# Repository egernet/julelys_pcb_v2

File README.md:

# Julelys PCB v3

HAT (Hardware Attached on Top) til Orange Pi Zero 2 til styring af adresserbare SK6812 RGBW LED-strips.

## System Oversigt

```
Orange Pi Zero 2 ──► Julelys HAT ──► 8×55 SK6812 LED Matrix (440 LEDs)
        │                 │
        │ SPI @ 2.5 Mbps  │
        ▼                 ▼
  julelys_manager    ESP32-C3 (SPI slave)
                          │
                          ▼
                    74HC4051 MUX + Level Shifters
                          │
                          ▼
                    8x JST outputs
```

## Relaterede Repositories

| Repository | Beskrivelse |
|------------|-------------|
| [julelys_manager](https://github.com/egernet/julelys_manager) | Swift CLI + MCP server til LED-styring |
| [julelys_esp32](https://github.com/egernet/julelys_esp32/tree/feature/Hat) | ESP-IDF firmware (feature/Hat branch) |

## Features

- **ESP32-C3-WROOM-02** som SPI slave med RMT LED driver
- **8 LED-kanaler** via 74HC4051 multiplexer
- **Level shifting** (3.3V → 5V) via 74AHCT1G125
- **USB-C** til strøm og programmering (CP2102N)
- **Auto-reset** kredsløb til nem flashing
- **AI-styring** via Model Context Protocol (MCP)

## Nøglekomponenter

| Komponent | Funktion |
|-----------|----------|
| ESP32-C3-WROOM-02 | Hoved-MCU, SPI slave |
| CP2102N | USB-UART bridge |
| AMS1117-3.3 | 5V → 3.3V LDO |
| 74HC4051 | 8-kanal analog multiplexer |
| 74AHCT1G125 ×4 | Level shifters |

## Connectors

| Reference | Type | Funktion |
|-----------|------|----------|
| J1 | 2×13 Pin Socket | Orange Pi GPIO header |
| J4-J11 | JST B3B-XH-A ×8 | LED strip outputs |
| P1 | USB-C | Strøm + programmering |
| V_IN1, V_IN2 | Skrueterminal ×2 | Ekstern 5V (parallel, ~20A) |

## Strømkrav

- **LED strøm:** 8 strenge × 55 LEDs × 60mA = **26.4A max**
- Brug ekstern 5V PSU med tilstrækkelig kapacitet
- Ingen reverse polarity protection (fjernet pga. strømkrav)

## KiCad Filer

- `Julelys.kicad_pcb` - PCB layout
- `Julelys.kicad_sch` - Hovedskema
- `esp32.kicad_sch` - ESP32 subskema
- `power.kicad_sch` - Strømforsyning
- `untitled.kicad_sch` - USB-C og connectors

## Produktion

Produktionsfiler genereres til `production/`:
- Gerber filer (zipped)
- `bom.csv` - Stykliste
- `positions.csv` - Pick and place

## Licens

MIT

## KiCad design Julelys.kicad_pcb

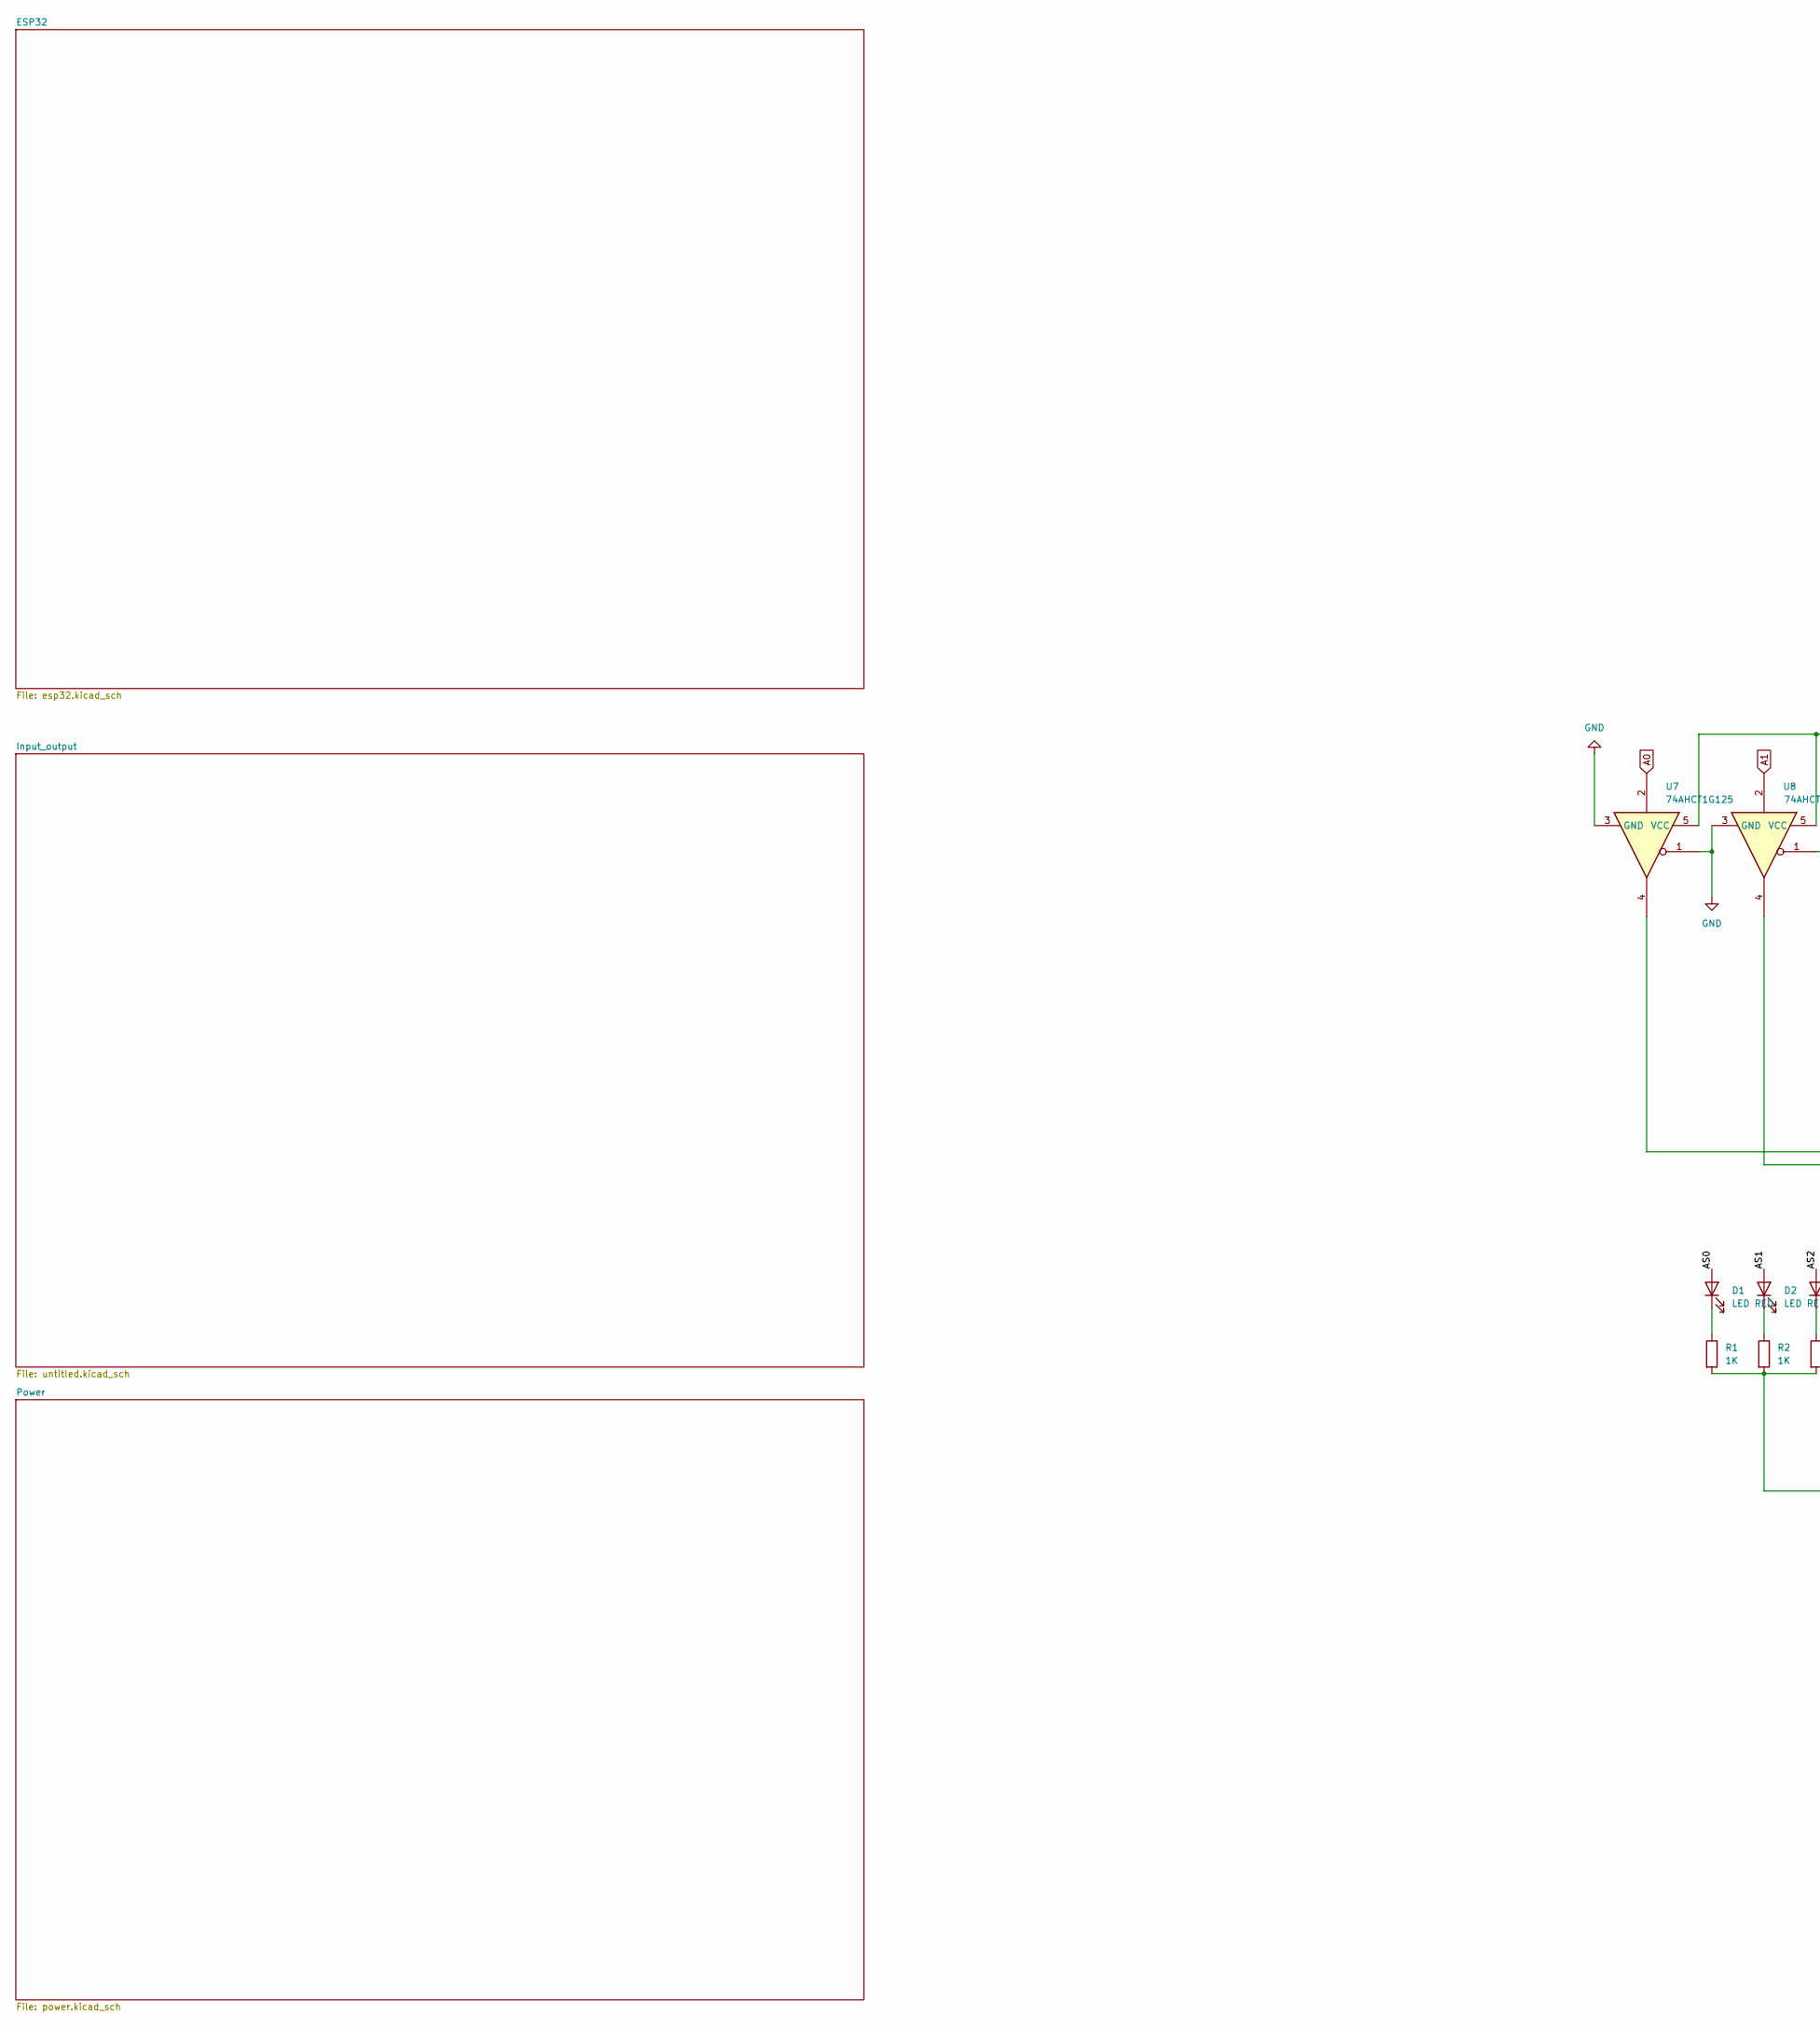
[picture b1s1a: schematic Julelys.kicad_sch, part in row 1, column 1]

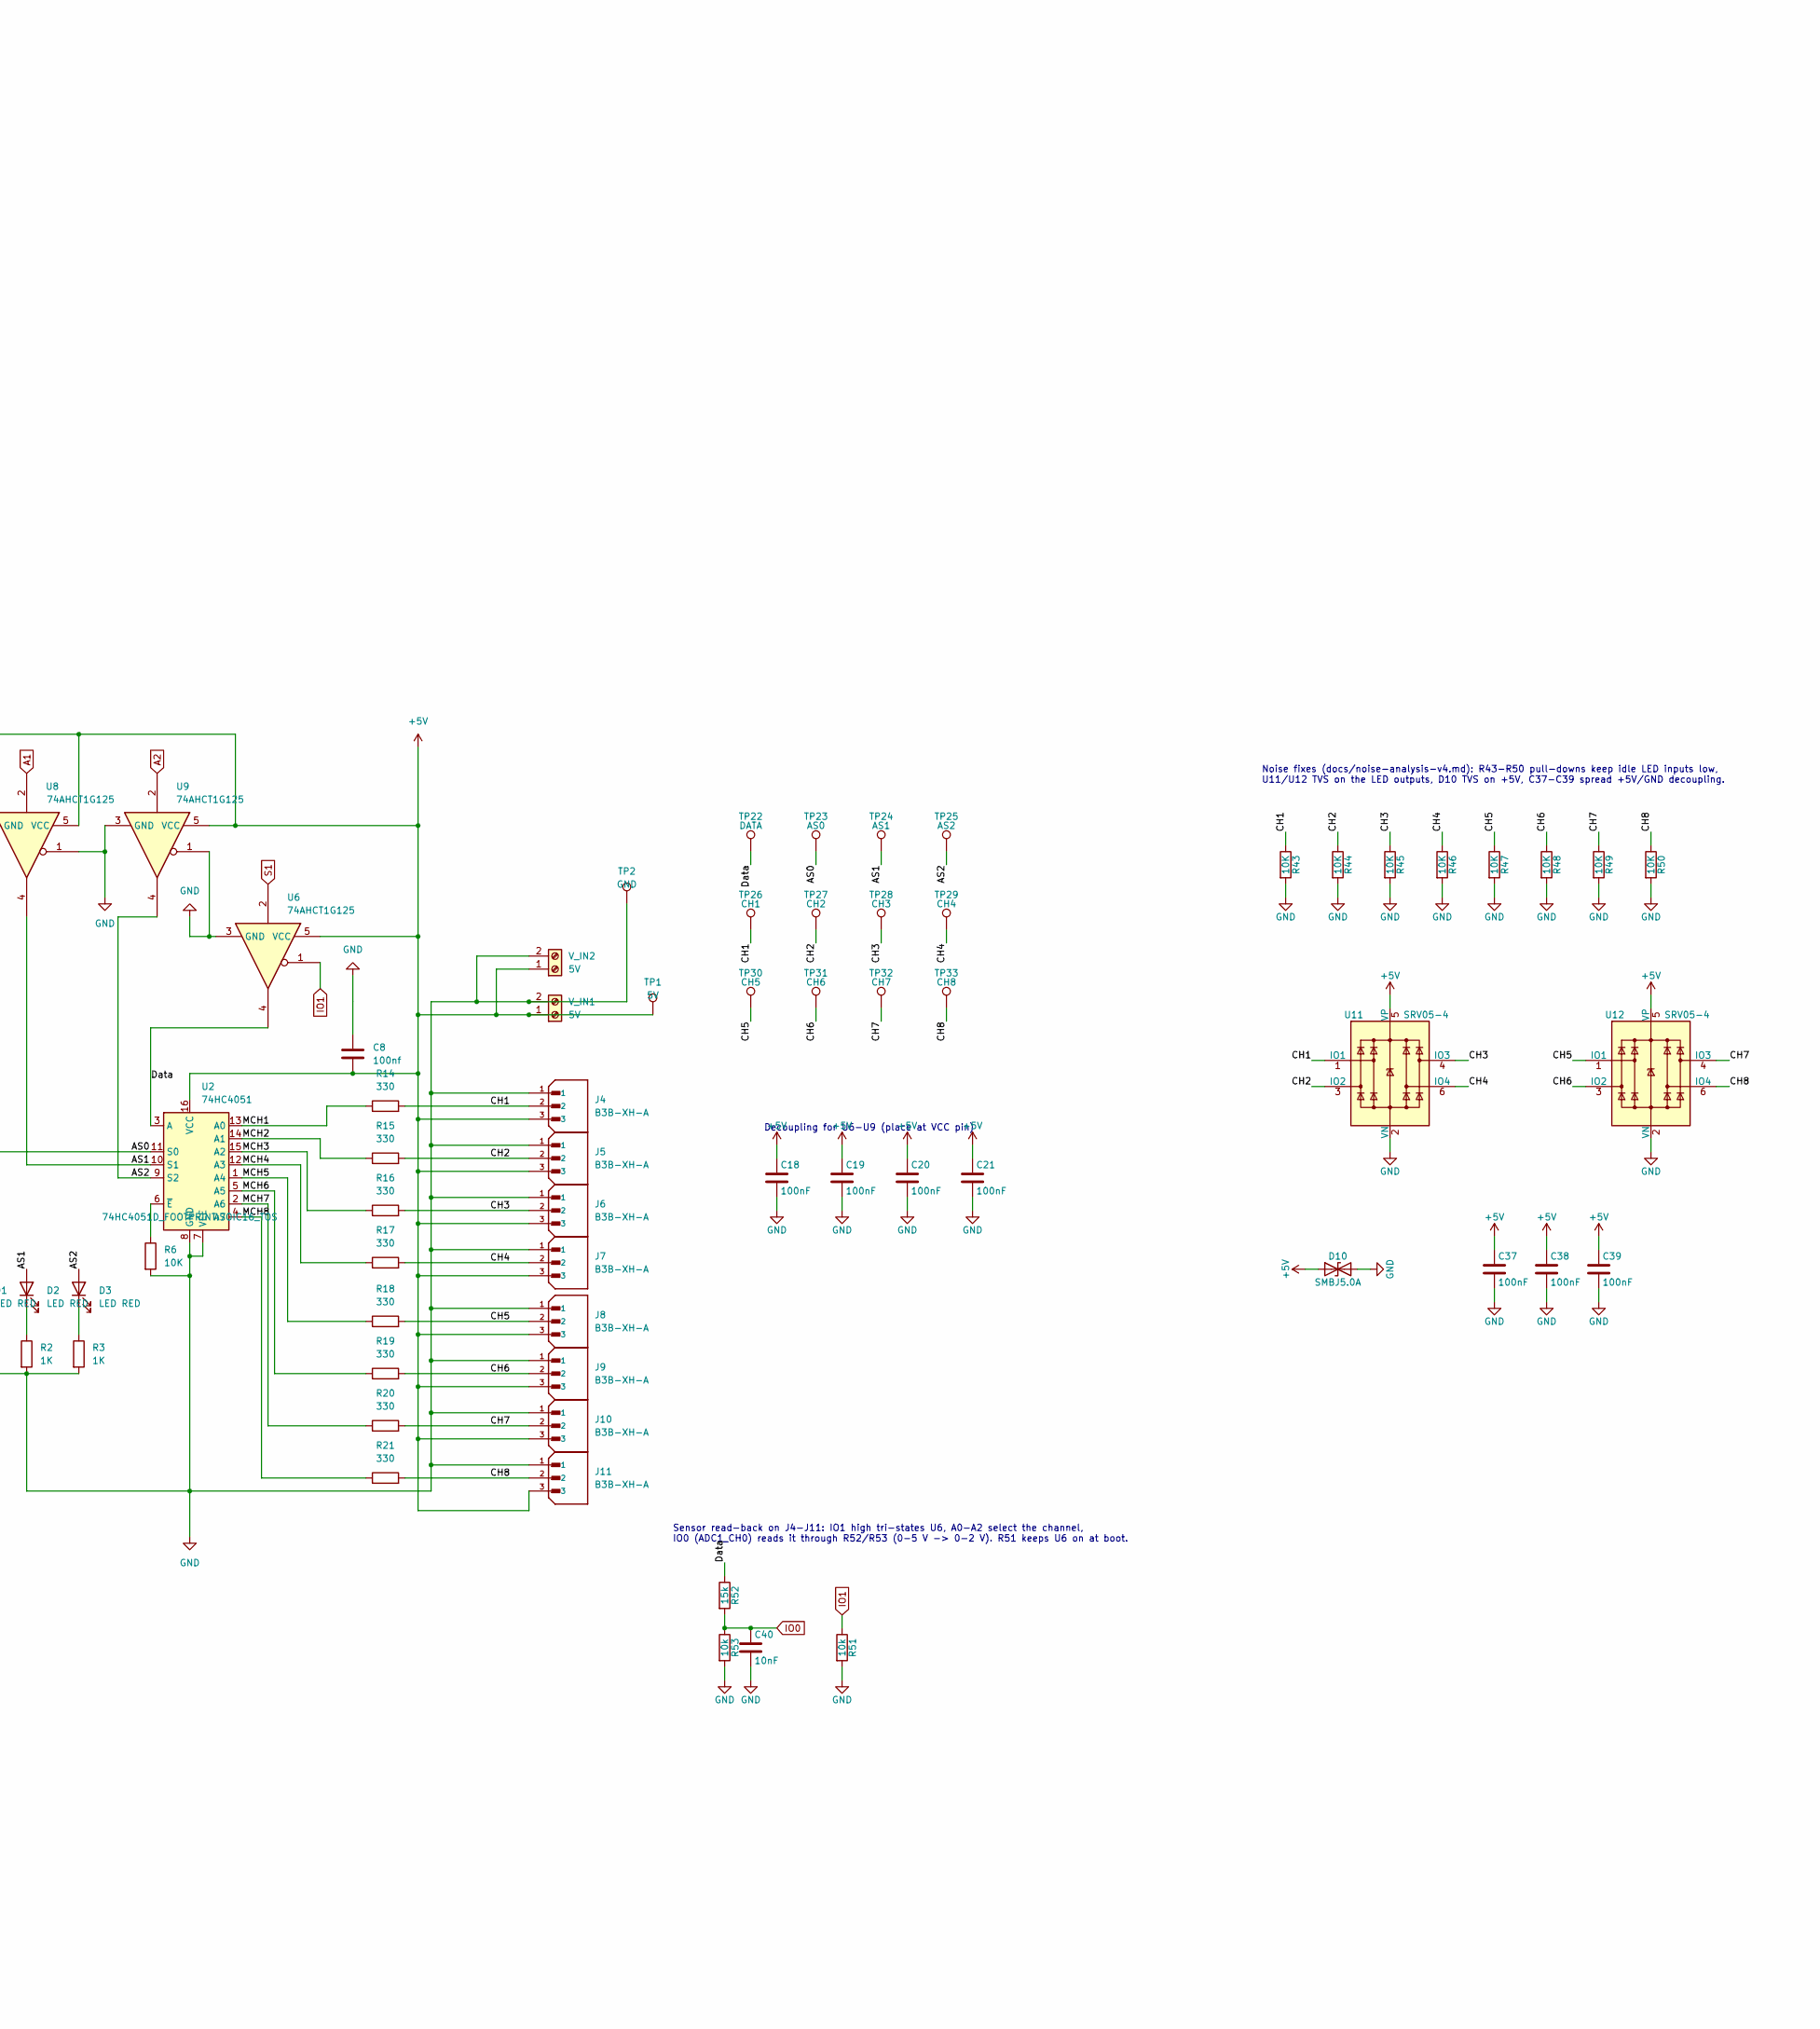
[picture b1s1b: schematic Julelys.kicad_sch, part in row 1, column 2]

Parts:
C8: 100nf; R_0603_1608Metric
C18, C19, C20, C21: 100nF; C_0603_1608Metric
C37, C38, C39: 100nF; C_0402_1005Metric
C40: 10nF; C_0402_1005Metric
D1, D2, D3: LED RED; LED_0805_2012Metric
D10: SMBJ5.0A; D_SMB
J4, J5, J6, J7, J8, J9, J10, J11: B3B-XH-A; JST_B3B-XH-A; PARTREV 7/4/21
R1, R2, R3: 1K; R_0603_1608Metric
R6: 10K; R_0603_1608Metric
R14, R15, R16, R17, R18, R19, R20, R21: 330; R_0603_1608Metric
R43, R44, R45, R46, R47, R48, R49, R50: 10K; R_0402_1005Metric
R51, R53: 10k; R_0402_1005Metric
R52: 15k; R_0402_1005Metric
TP1: 5V; TestPoint_Pad_1.0x1.0mm
TP2: GND; TestPoint_Pad_1.0x1.0mm
TP22: DATA; TestPoint_Pad_1.0x1.0mm
TP23: AS0; TestPoint_Pad_1.0x1.0mm
TP24: AS1; TestPoint_Pad_1.0x1.0mm
TP25: AS2; TestPoint_Pad_1.0x1.0mm
TP26: CH1; TestPoint_Pad_1.0x1.0mm
TP27: CH2; TestPoint_Pad_1.0x1.0mm
TP28: CH3; TestPoint_Pad_1.0x1.0mm
TP29: CH4; TestPoint_Pad_1.0x1.0mm
TP30: CH5; TestPoint_Pad_1.0x1.0mm
TP31: CH6; TestPoint_Pad_1.0x1.0mm
TP32: CH7; TestPoint_Pad_1.0x1.0mm
TP33: CH8; TestPoint_Pad_1.0x1.0mm
U2: 74HC4051; SOIC16_TOS
U6, U7, U8, U9: 74AHCT1G125; SOT-353_SC-70-5
U11, U12: SRV05-4; SOT-23-6
V_IN1, V_IN2: 5V; TerminalBlock_Altech_AK300-2_P5.00mm

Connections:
+5V: C8.2, C18.1, C19.1, C20.1, C21.1, C37.1, C38.1, C39.1, D10.1 (A1), J4.3, J5.3, J6.3, J7.3, J8.3, J9.3, J10.3, J11.3, TP1.1, U2.16 (VCC), U6.5 (VCC), U7.5 (VCC), U8.5 (VCC), U9.5 (VCC), U11.5 (VP), U12.5 (VP), V_IN1.1, V_IN2.1; also elsewhere on the board
/AS0: D1.2 (A), TP23.1, U2.11 (S0), U7.4
/AS1: D2.2 (A), TP24.1, U2.10 (S1), U8.4
/AS2: D3.2 (A), TP25.1, U2.9 (S2), U9.4
/CH1: J4.2, R14.2, R43.1, TP26.1, U11.1 (IO1)
/CH2: J5.2, R15.2, R44.1, TP27.1, U11.3 (IO2)
/CH3: J6.2, R16.2, R45.1, TP28.1, U11.4 (IO3)
/CH4: J7.2, R17.2, R46.1, TP29.1, U11.6 (IO4)
/CH5: J8.2, R18.2, R47.1, TP30.1, U12.1 (IO1)
/CH6: J9.2, R19.2, R48.1, TP31.1, U12.3 (IO2)
/CH7: J10.2, R20.2, R49.1, TP32.1, U12.4 (IO3)
/CH8: J11.2, R21.2, R50.1, TP33.1, U12.6 (IO4)
/Data: R52.1, TP22.1, U2.3 (A), U6.4
/MCH1: R14.1, U2.13 (A0)
/MCH2: R15.1, U2.14 (A1)
/MCH3: R16.1, U2.15 (A2)
/MCH4: R17.1, U2.12 (A3)
/MCH5: R18.1, U2.1 (A4)
/MCH6: R19.1, U2.5 (A5)
/MCH7: R20.1, U2.2 (A6)
/MCH8: R21.1, U2.4 (A7)
A0: U7.2; also elsewhere on the board
A1: U8.2; also elsewhere on the board
A2: U9.2; also elsewhere on the board
GND: C8.1, C18.2, C19.2, C20.2, C21.2, C37.2, C38.2, C39.2, C40.2, D10.2 (A2), J4.1, J5.1, J6.1, J7.1, J8.1, J9.1, J10.1, J11.1, R1.2, R2.2, R3.2, R6.2, R43.2, R44.2, R45.2, R46.2, R47.2, R48.2, R49.2, R50.2, R51.2, R53.2, TP2.1, U2.7 (VEE), U2.8 (GND), U6.3 (GND), U7.1, U7.3 (GND), U8.1, U8.3 (GND), U9.1, U9.3 (GND), U11.2 (VN), U12.2 (VN), V_IN1.2, V_IN2.2; also elsewhere on the board
IO0: C40.1, R52.2, R53.1; also elsewhere on the board
IO1: R51.1, U6.1; also elsewhere on the board
IO7: U6.2; also elsewhere on the board
unnamed: D1.1 (K), R1.1
unnamed: D2.1 (K), R2.1
unnamed: D3.1 (K), R3.1
unnamed: R6.1, U2.6 (~E)

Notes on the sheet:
Decoupling for U6-U9 (place at VCC pin)
Noise fixes (docs/noise-analysis-v4.md): R43-R50 pull-downs keep idle LED inputs low, U11/U12 TVS on the LED outputs, D10 TVS on +5V, C37-C39 spread +5V/GND decoupling.
Sensor read-back on J4-J11: IO1 high tri-states U6, A0-A2 select the channel, IO0 (ADC1_CH0) reads it through R52/R53 (0-5 V -> 0-2 V). R51 keeps U6 on at boot.

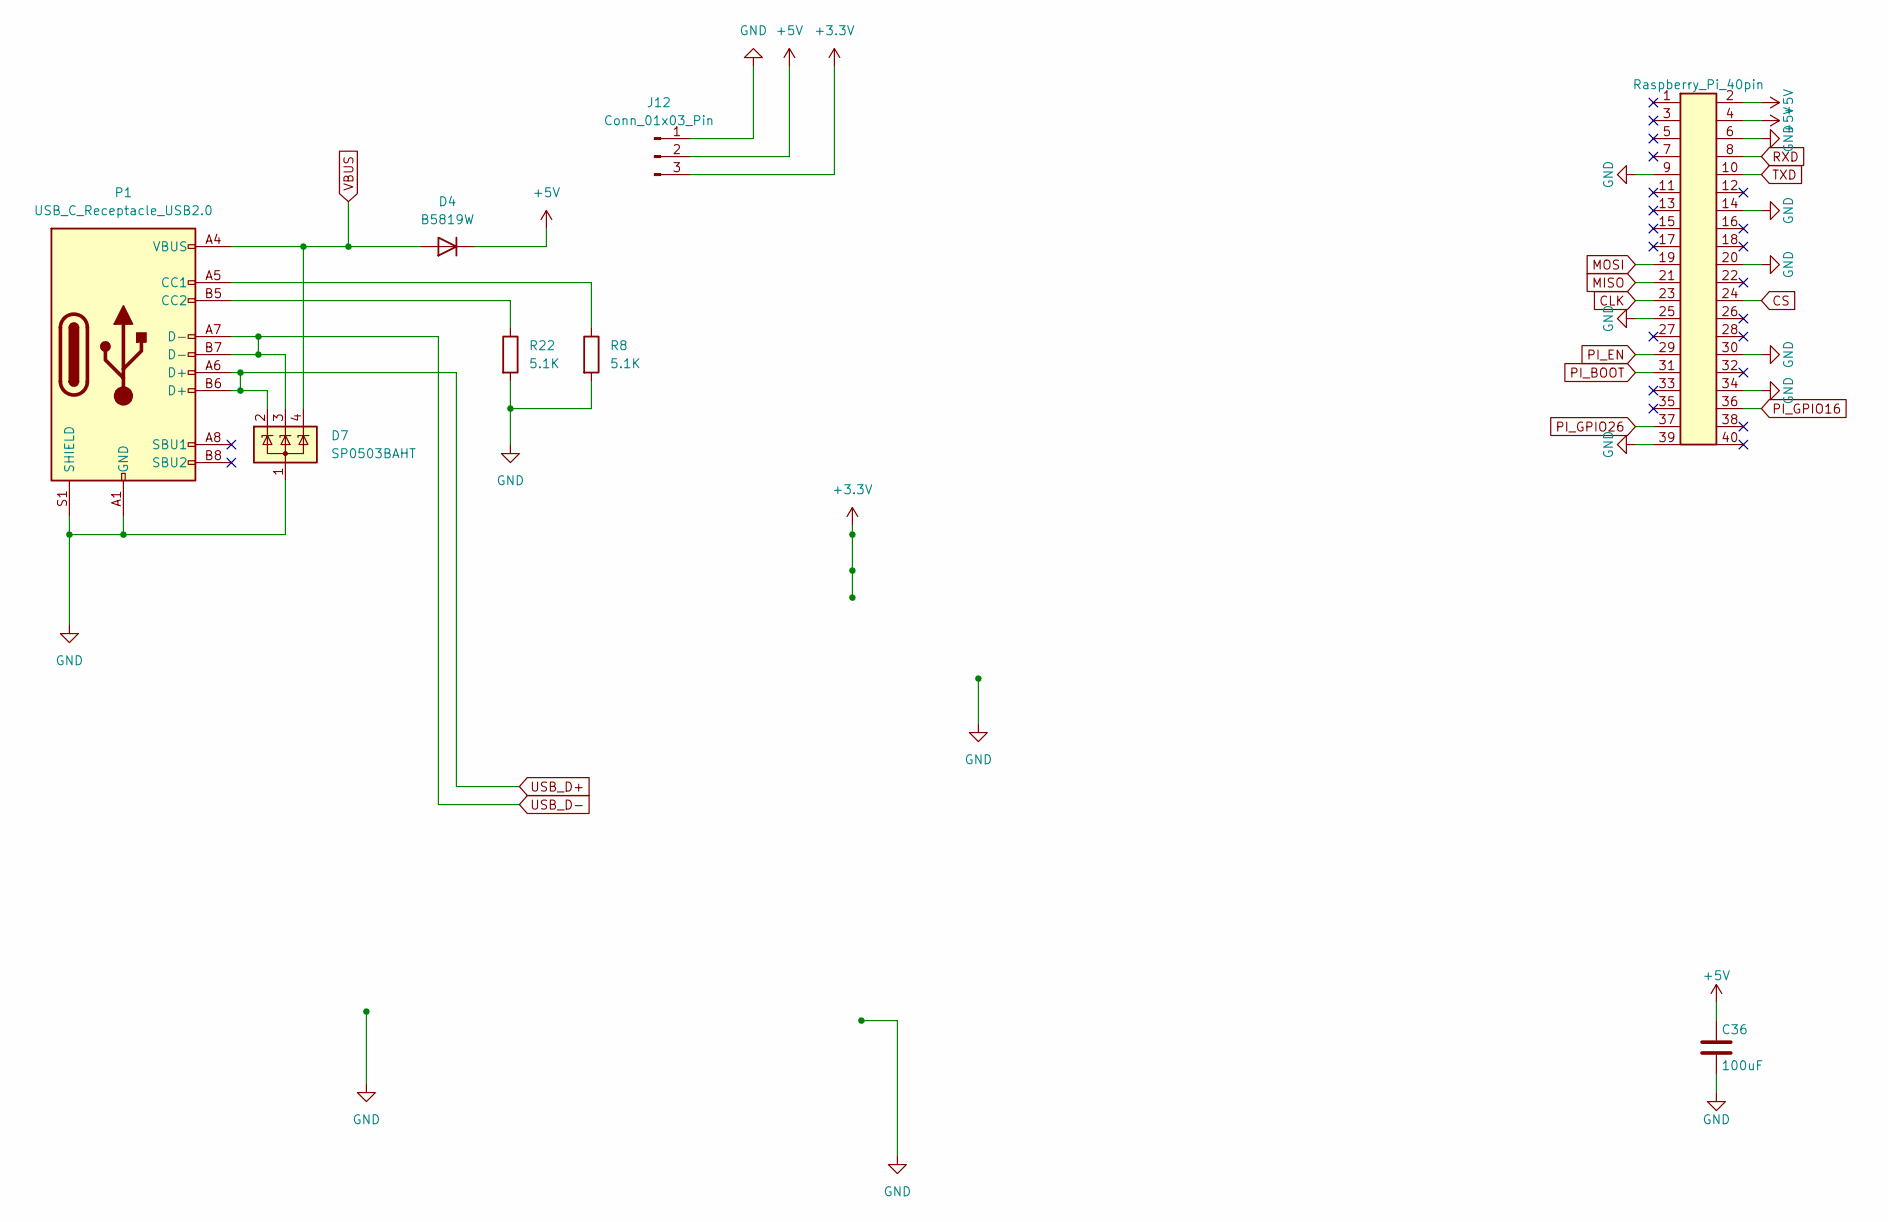
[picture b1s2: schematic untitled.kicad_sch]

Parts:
C36: 100uF; C_1206_3216Metric
D4: B5819W; D_SOD-123
D7: SP0503BAHT; SOT-143
J1: Raspberry_Pi_40pin; PinSocket_2x20_P2.54mm_Vertical
J12: Conn_01x03_Pin; PinHeader_1x03_P2.54mm_Vertical
P1: USB_C_Receptacle_USB2.0; USB_C_Receptacle_HRO_TYPE-C-31-M-12
R8, R22: 5.1K; R_0603_1608Metric

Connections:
+3.3V: J12.3; also elsewhere on the board
+5V: C36.1, D4.1 (K), J1.2, J1.4, J12.2; also elsewhere on the board
CLK: J1.23; also elsewhere on the board
CS: J1.24; also elsewhere on the board
GND: C36.2, D7.1 (A), J1.6, J1.9, J1.14, J1.20, J1.25, J1.30, J1.34, J1.39, J12.1, P1.A1 (GND), P1.A12 (GND), P1.B1 (GND), P1.B12 (GND), P1.S1 (SHIELD), R8.2, R22.2; also elsewhere on the board
IO2: J1.21; also elsewhere on the board
IO6: J1.19; also elsewhere on the board
unnamed: P1.A5 (CC1), R8.1
unnamed: P1.B5 (CC2), R22.1
PI_BOOT: J1.31; also elsewhere on the board
PI_EN: J1.29; also elsewhere on the board
PI_GPIO16: J1.36; also elsewhere on the board
PI_GPIO26: J1.37; also elsewhere on the board
RXD: J1.8; also elsewhere on the board
TXD: J1.10; also elsewhere on the board
USB_D+: D7.2 (K), P1.A6 (D+), P1.B6 (D+); also elsewhere on the board
USB_D-: D7.3 (K), P1.A7 (D-), P1.B7 (D-); also elsewhere on the board
VBUS: D4.2 (A), D7.4 (K), P1.A4 (VBUS), P1.A9 (VBUS), P1.B4 (VBUS), P1.B9 (VBUS); also elsewhere on the board

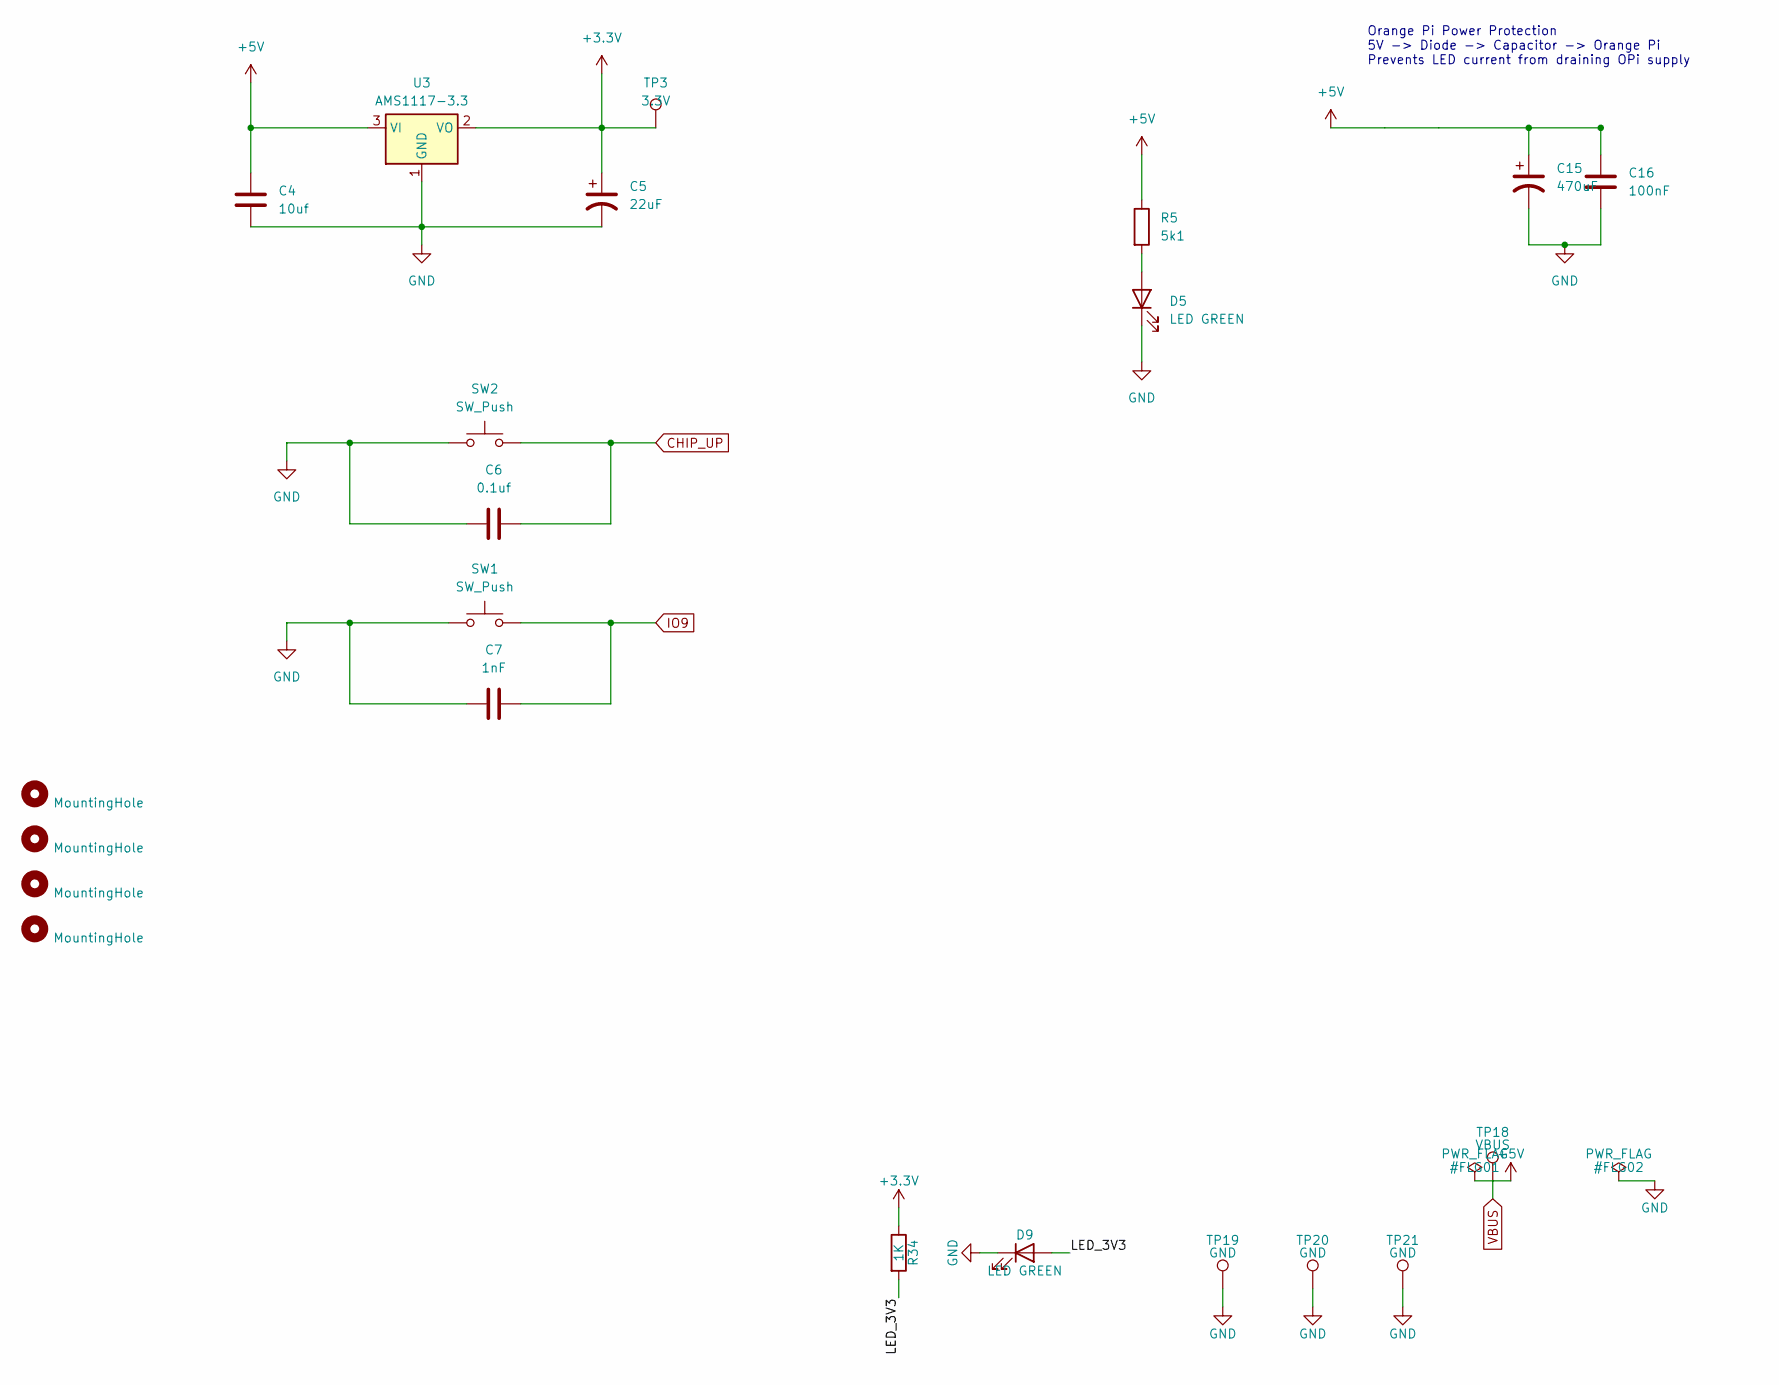
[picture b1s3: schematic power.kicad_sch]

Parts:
C4: 10uf; C_0603_1608Metric
C5: 22uF; C_0603_1608Metric
C6: 0.1uf; C_0603_1608Metric
C7: 1nF; C_0603_1608Metric
C15: 470uF; CP_Elec_8x10
C16: 100nF; C_0603_1608Metric
D5, D9: LED GREEN; LED_0805_2012Metric
H1, H2, H3, H4: MountingHole; MountingHole_2.7mm_M2.5
R5: 5k1; R_0603_1608Metric
R34: 1K; R_0603_1608Metric
SW1, SW2: SW_Push; SW_SPST_TL3305A
TP3: 3.3V; TestPoint_Pad_1.0x1.0mm
TP18: VBUS; TestPoint_Pad_1.0x1.0mm
TP19, TP20, TP21: GND; TestPoint_Pad_1.0x1.0mm
U3: AMS1117-3.3; SOT-223-3_TabPin2

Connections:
+3.3V: C5.1, R34.1, TP3.1, U3.2 (VO); also elsewhere on the board
+5V: C4.1, C15.1, C16.1, R5.1, U3.3 (VI); also elsewhere on the board
/Power/LED_3V3: D9.2 (A), R34.2
CHIP_UP: C6.2, SW2.2; also elsewhere on the board
GND: C4.2, C5.2, C6.1, C7.1, C15.2, C16.2, D5.1 (K), D9.1 (K), SW1.1, SW2.1, TP19.1, TP20.1, TP21.1, U3.1 (GND); also elsewhere on the board
IO9: C7.2, SW1.2; also elsewhere on the board
unnamed: D5.2 (A), R5.2
VBUS: TP18.1; also elsewhere on the board

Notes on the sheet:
Orange Pi Power Protection 5V -> Diode -> Capacitor -> Orange Pi Prevents LED current from draining OPi supply

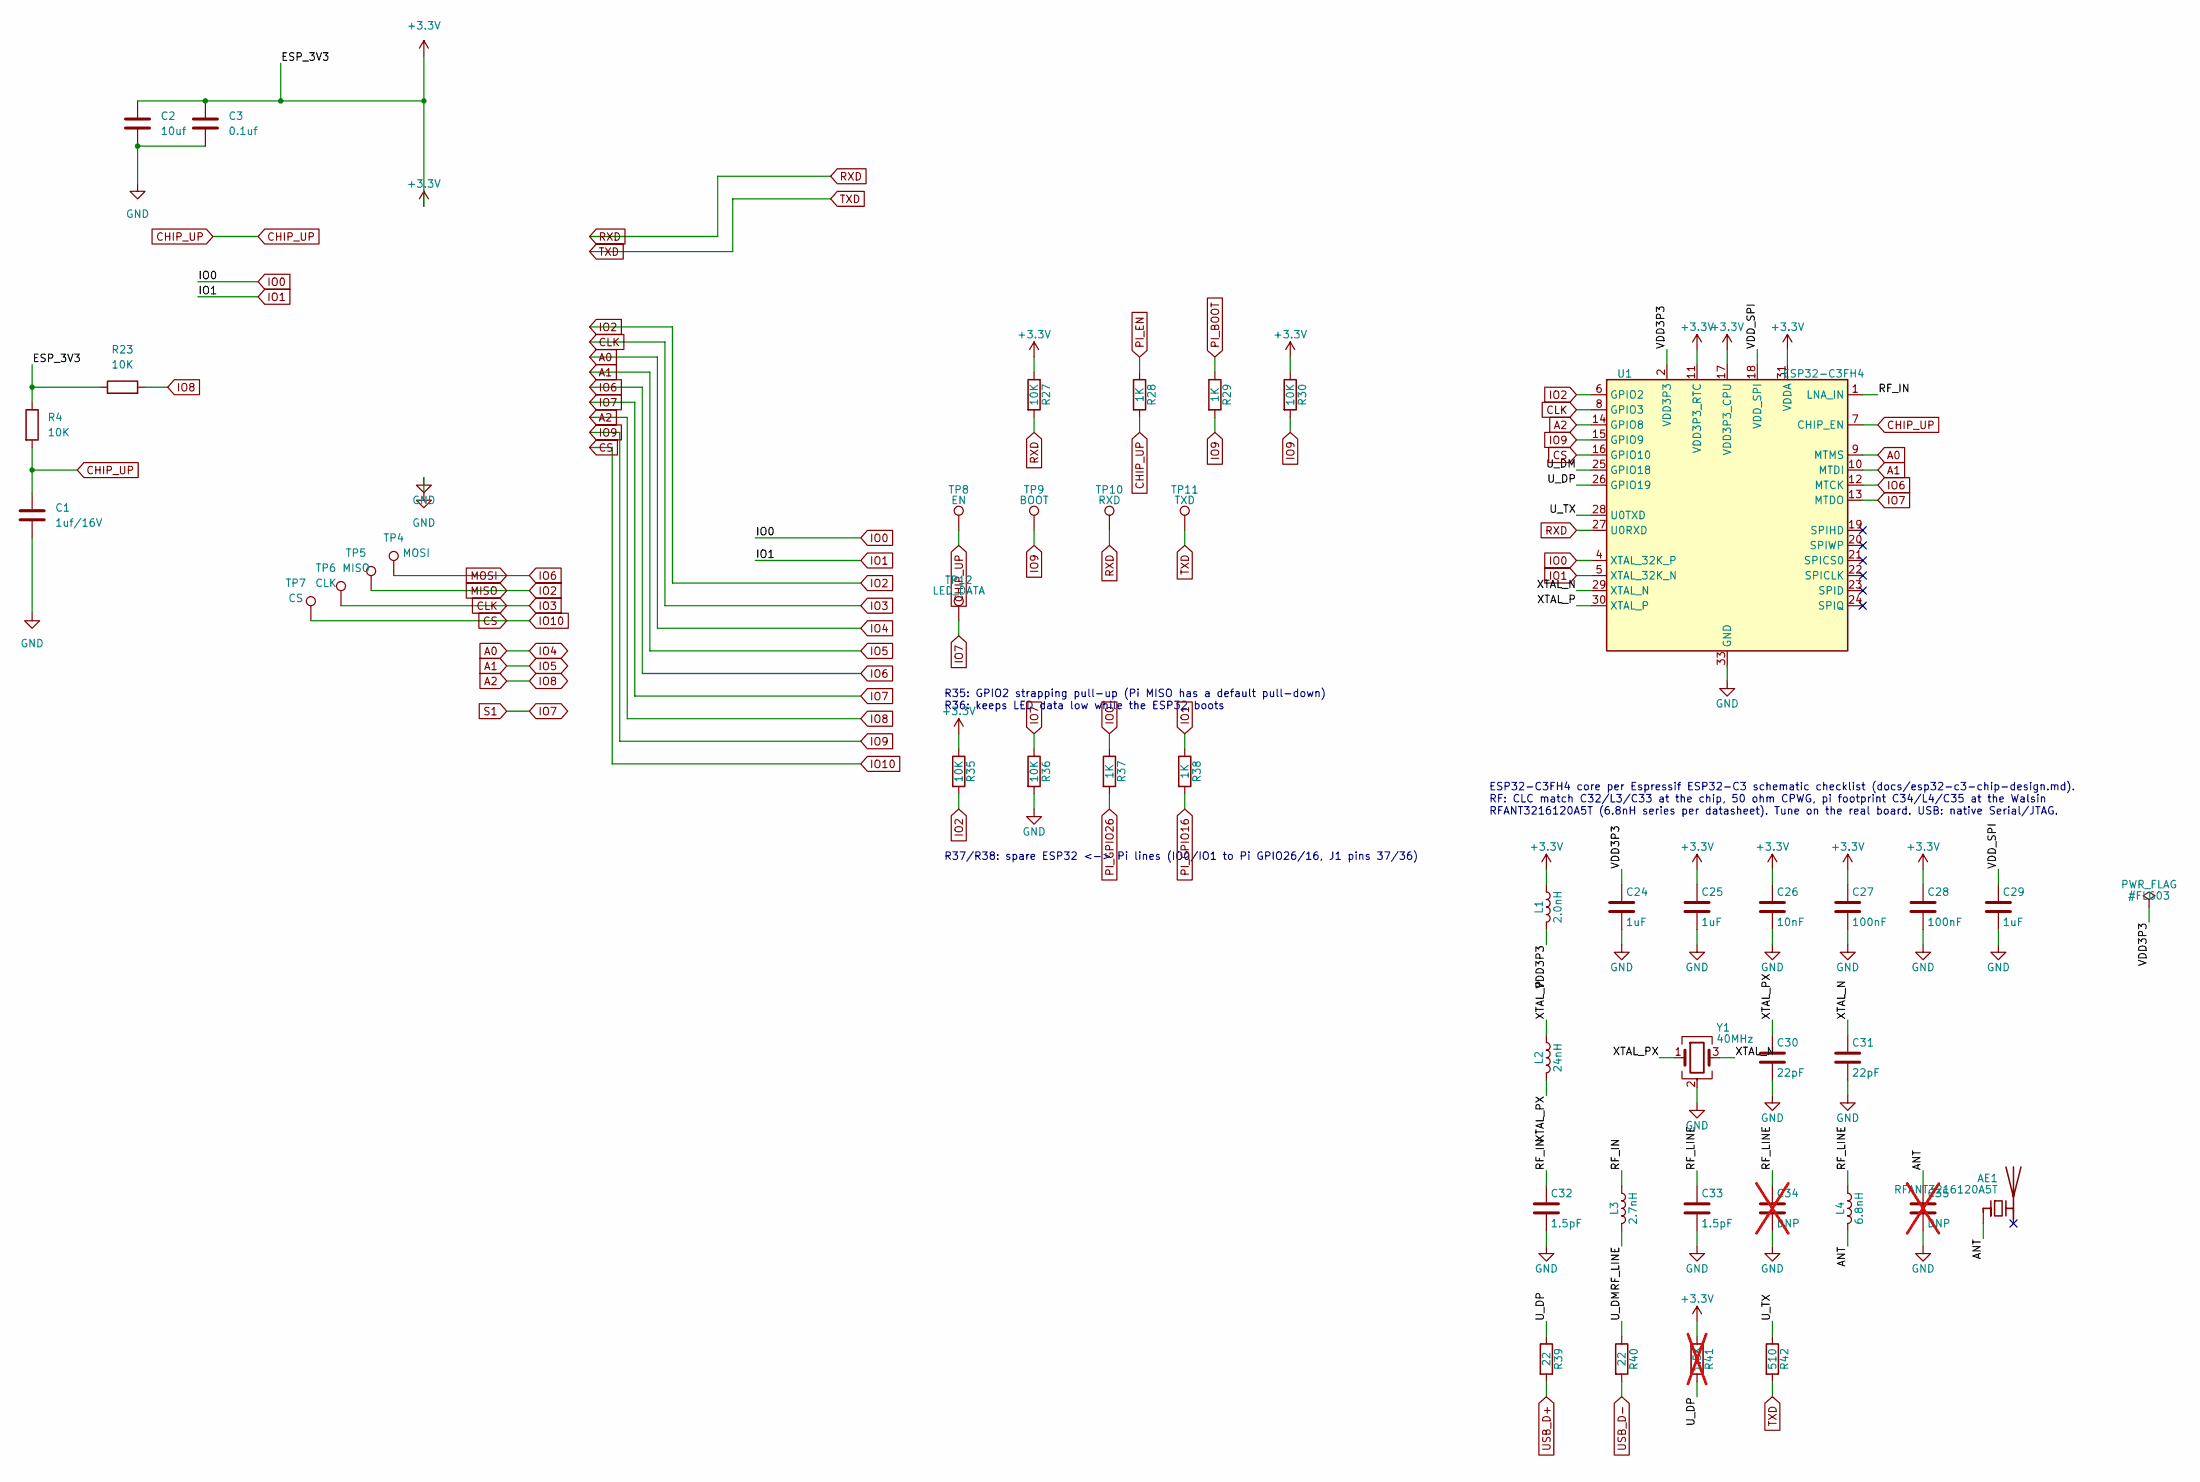
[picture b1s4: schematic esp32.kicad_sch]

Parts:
AE1: RFANT3216120A5T; Walsin_RFANT3216120A5T
C1: 1uf/16V; C_0603_1608Metric
C2: 10uf; C_0603_1608Metric
C3: 0.1uf; C_0603_1608Metric
C24, C25, C29: 1uF; C_0402_1005Metric
C26: 10nF; C_0402_1005Metric
C27, C28: 100nF; C_0402_1005Metric
C30, C31: 22pF; C_0402_1005Metric
C32, C33: 1.5pF; C_0402_1005Metric
C34, C35: DNP; C_0402_1005Metric; not fitted
L1: 2.0nH; L_0402_1005Metric
L2: 24nH; L_0402_1005Metric
L3: 2.7nH; L_0402_1005Metric
L4: 6.8nH; L_0402_1005Metric
R4, R23, R27, R30, R35, R36: 10K; R_0603_1608Metric
R28, R29, R37, R38: 1K; R_0603_1608Metric
R39, R40: 22; R_0402_1005Metric
R41: 1.5K; R_0402_1005Metric; not fitted
R42: 510; R_0402_1005Metric
TP4: MOSI; TestPoint_Pad_1.0x1.0mm
TP5: MISO; TestPoint_Pad_1.0x1.0mm
TP6: CLK; TestPoint_Pad_1.0x1.0mm
TP7: CS; TestPoint_Pad_1.0x1.0mm
TP8: EN; TestPoint_Pad_1.0x1.0mm
TP9: BOOT; TestPoint_Pad_1.0x1.0mm
TP10: RXD; TestPoint_Pad_1.0x1.0mm
TP11: TXD; TestPoint_Pad_1.0x1.0mm
TP12: LED_DATA; TestPoint_Pad_1.0x1.0mm
U1: ESP32-C3FH4; QFN-32-1EP_5x5mm_P0.5mm_EP3.7x3.7mm
Y1: 40MHz; Crystal_SMD_3225-4Pin_3.2x2.5mm

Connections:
+3.3V: C2.1, C3.1, C25.1, C26.1, C27.1, C28.1, L1.1, R4.1, R23.1, R27.1, R30.1, R35.1, R41.1, U1.11 (VDD3P3_RTC), U1.17 (VDD3P3_CPU), U1.31 (VDDA), U1.32 (VDDA); also elsewhere on the board
/ESP32/ANT: AE1.1 (FEED), C35.1, L4.2
/ESP32/RF_IN: C32.1, L3.1, U1.1 (LNA_IN)
/ESP32/RF_LINE: C33.1, C34.1, L3.2, L4.1
/ESP32/U_DM: R40.1, U1.25 (GPIO18)
/ESP32/U_DP: R39.1, R41.2, U1.26 (GPIO19)
/ESP32/U_TX: R42.1, U1.28 (U0TXD)
/ESP32/VDD3P3: C24.1, L1.2, U1.2 (VDD3P3), U1.3 (VDD3P3)
/ESP32/VDD_SPI: C29.1, U1.18 (VDD_SPI)
/ESP32/XTAL_N: C31.1, U1.29 (XTAL_N), Y1.3
/ESP32/XTAL_P: L2.1, U1.30 (XTAL_P)
/ESP32/XTAL_PX: C30.1, L2.2, Y1.1
A0: U1.9 (MTMS); also elsewhere on the board
A1: U1.10 (MTDI); also elsewhere on the board
A2: R23.2, U1.14 (GPIO8); also elsewhere on the board
CHIP_UP: C1.1, R4.2, R28.2, TP8.1, U1.7 (CHIP_EN); also elsewhere on the board
CLK: TP6.1, U1.8 (GPIO3); also elsewhere on the board
CS: TP7.1, U1.16 (GPIO10); also elsewhere on the board
GND: C1.2, C2.2, C3.2, C24.2, C25.2, C26.2, C27.2, C28.2, C29.2, C30.2, C31.2, C32.2, C33.2, C34.2, C35.2, R36.2, U1.33 (GND), Y1.2 (G), Y1.4 (G); also elsewhere on the board
IO0: R37.1, U1.4 (XTAL_32K_P); also elsewhere on the board
IO1: R38.1, U1.5 (XTAL_32K_N); also elsewhere on the board
IO2: R35.2, TP5.1, U1.6 (GPIO2); also elsewhere on the board
IO6: TP4.1, U1.12 (MTCK); also elsewhere on the board
IO7: R36.1, TP12.1, U1.13 (MTDO); also elsewhere on the board
IO9: R29.2, R30.2, TP9.1, U1.15 (GPIO9); also elsewhere on the board
PI_BOOT: R29.1; also elsewhere on the board
PI_EN: R28.1; also elsewhere on the board
PI_GPIO16: R38.2; also elsewhere on the board
PI_GPIO26: R37.2; also elsewhere on the board
RXD: R27.2, TP10.1, U1.27 (U0RXD); also elsewhere on the board
TXD: R42.2, TP11.1; also elsewhere on the board
USB_D+: R39.2; also elsewhere on the board
USB_D-: R40.2; also elsewhere on the board

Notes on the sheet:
R35: GPIO2 strapping pull-up (Pi MISO has a default pull-down) R36: keeps LED data low while the ESP32 boots
R37/R38: spare ESP32 <-> Pi lines (IO0/IO1 to Pi GPIO26/16, J1 pins 37/36)
ESP32-C3FH4 core per Espressif ESP32-C3 schematic checklist (docs/esp32-c3-chip-design.md). RF: CLC match C32/L3/C33 at the chip, 50 ohm CPWG, pi footprint C34/L4/C35 at the Walsin RFANT3216120A5T (6.8nH series per datasheet). Tune on the real board. USB: native Serial/JTAG.
